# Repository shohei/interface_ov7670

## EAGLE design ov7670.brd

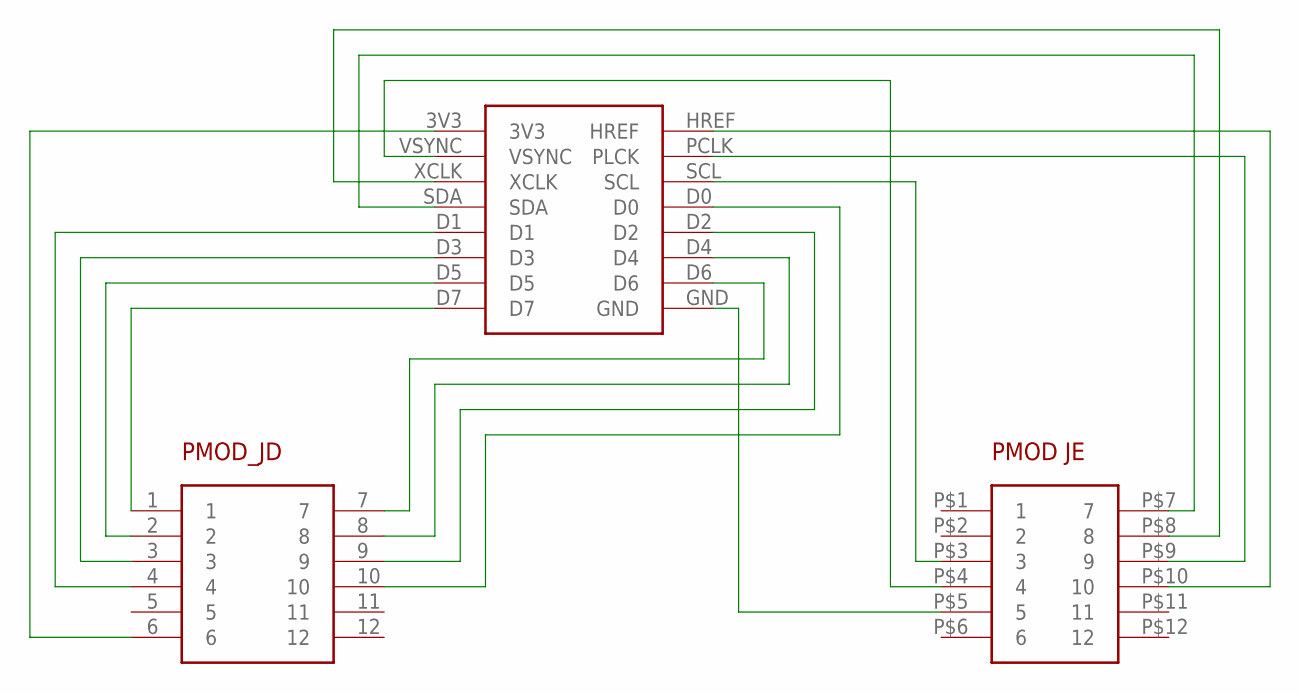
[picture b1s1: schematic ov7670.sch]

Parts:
D6: OV7670
U$2: PMOD_JD
U$3: PMOD_JE

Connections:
3V3: D6.3V3, U$2.6
D0: D6.D0, U$2.10
D1: D6.D1, U$2.4
D2: D6.D2, U$2.9
D3: D6.D3, U$2.3
D4: D6.D4, U$2.8
D5: D6.D5, U$2.2
D7: D6.D7, U$2.1
GND: D6.GND, U$3.P$5 (5)
HREF: D6.HREF, U$3.P$10 (10)
unnamed: D6.D6, U$2.7
PCLK: D6.PCLK (PLCK), U$3.P$9 (9)
SCL: D6.SCL, U$3.P$3 (3)
SDA: D6.SDA, U$3.P$7 (7)
VSYNC: D6.VSYNC, U$3.P$4 (4)
XCLK: D6.XCLK, U$3.P$8 (8)

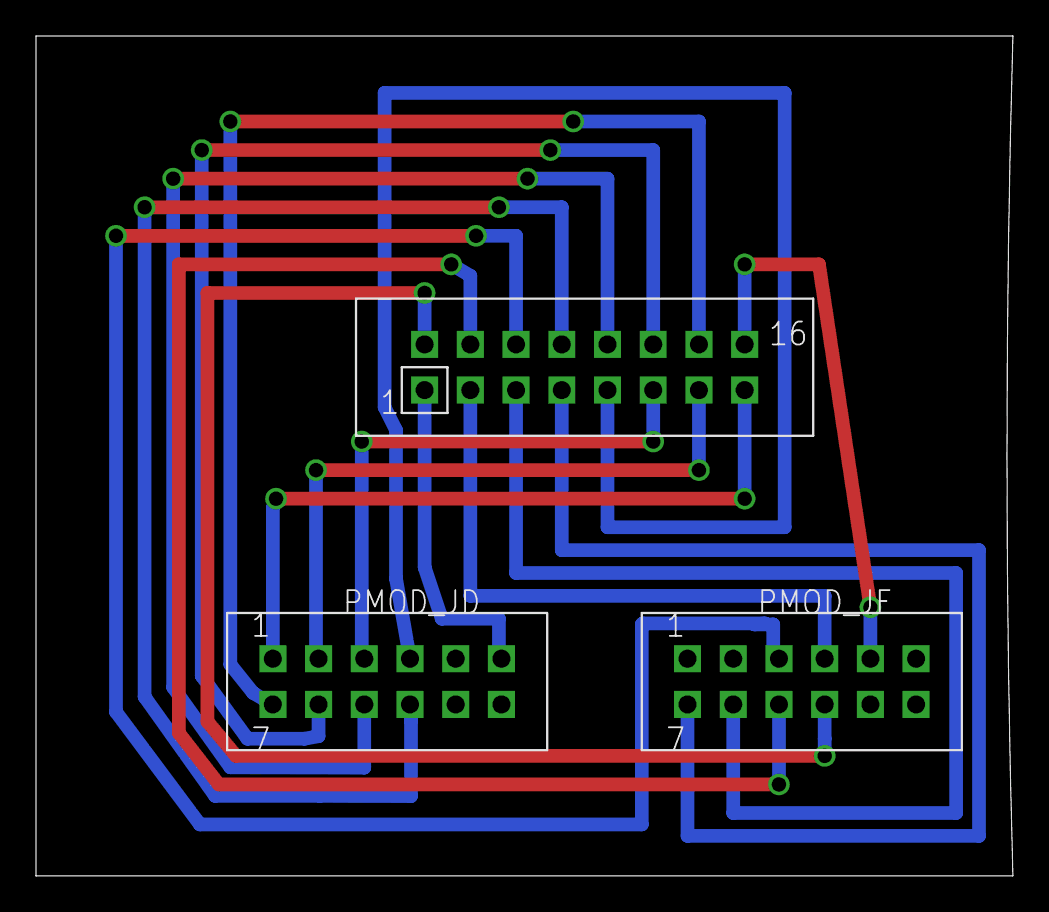
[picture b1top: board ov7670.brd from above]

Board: 2 copper layers, 54.3 x 46.7 mm, 3 parts (0 on the bottom side), 16 nets.

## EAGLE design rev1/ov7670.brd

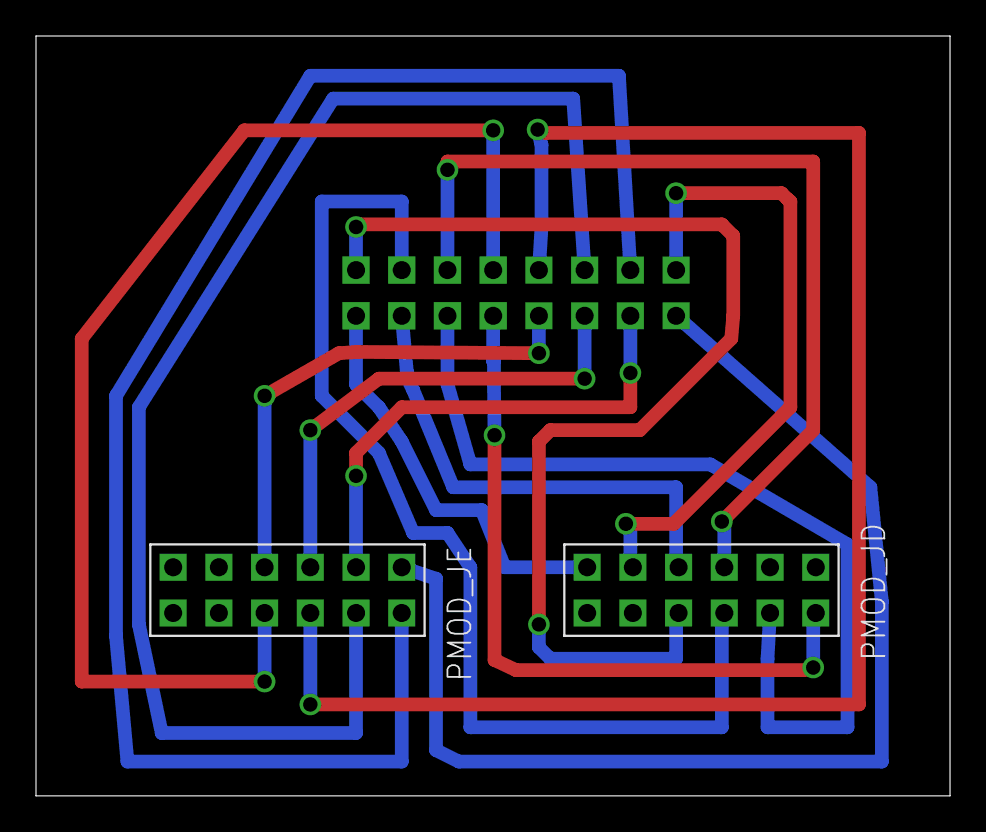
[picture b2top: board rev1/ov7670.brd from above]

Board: 2 copper layers, 50.8 x 42.2 mm, 3 parts (0 on the bottom side), 16 nets.

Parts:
U$1: OV7670
U$2: PMOD_JD
U$3: PMOD_JE

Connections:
3V3: U$1.3V3, U$2.6
D0: U$1.D0, U$3.10
D1: U$1.D1, U$3.4
D2: U$1.D2, U$3.9
D3: U$1.D3, U$3.3
D4: U$1.D4, U$3.8
D5: U$1.D5, U$3.2
D6: U$1.D6, U$3.7
D7: U$1.D7, U$3.1
GND: U$1.GND, U$2.5
HREF: U$1.HREF, U$2.10
PLCK: U$1.PLCK, U$2.9
SCL: U$1.SCL, U$2.3
SDA: U$1.SDA, U$2.7
VSYNC: U$1.VSYNC, U$2.4
XCLK: U$1.XCLK, U$2.8

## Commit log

2017-11-09 add cam files
2017-11-09 add cam
2017-11-10 update design
2017-11-10 add photos
2017-11-10 update image
2017-11-10 update to rev2
2017-11-16 temporal commit
2017-11-16 update gerver image
2017-11-22 add pcb
2017-11-22 add linguist-ignore
